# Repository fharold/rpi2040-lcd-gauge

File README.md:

# universal_gauges

Basic and versatile gauges based on the WAVESHARE RP2040-LCD-1.28 module.
A small HAT enhances it:

- 2 analog sensor inputs (divider stuffed to suit the sender, 5 V supply)
- 2 digital inputs (level shifted)
- 1 ambient light sensor
- 1 button
- 2 relay outputs

The firmware sources are in the repository root; the HAT itself is a KiCad
project in `pcb/`, described in [The HAT board](#the-hat-board).

The target is the **RP2040-LCD-1.28**. The touch variant is not supported: its
user button sits on GP16, which the HAT uses for its first digital input, so
the two would share one pin.

## Pinout

Signals added by the HAT:

| GPIO | Signal | Direction |
| ---- | ------ | --------- |
| GP16 | shifted_digital_in1 | input |
| GP17 | shifted_digital_in2 | input |
| GP18 | button_input | input, pull-up |
| GP19 | relay1_command_pin | output |
| GP20 | relay2_command_pin | output |
| GP26 | als_out | analog input, ADC0 |
| GP27 | sensor2_filtered | analog input, ADC1 |
| GP28 | sensor1_filtered | analog input, ADC2 |

The RP2040 ADC channel is not the GPIO number: GP26 is ADC0, GP27 is ADC1,
GP28 is ADC2, and GP29 (ADC3) is the module's own battery sense.

Pins used by the module itself (display, I2C, IMU, backlight, battery) are
defined in `lib/lcd/lcd.h`.

## The HAT board

The HAT is a KiCad 10 project, `pcb/rpi2040-lcd-gauge.kicad_pro`: a two-layer
board, 1.6 mm, 35 x 38.7 mm, whose lower edge is a semicircle following the
module. It sits
behind the RP2040-LCD-1.28 and connects to it through J2, a 2x10 1.27 mm
header. J1 is the header on the other side of the module; it is mechanical
only, none of its pads is connected.

The schematic is hierarchical, one sheet per function:

| Sheet | File | Contents |
| ----- | ---- | -------- |
| psu | `PSU.kicad_sch` | input protection, 12 V -> 5 V buck |
| ain_1, ain_2 | `sensor_1.kicad_sch`, `sensor_2.kicad_sch` | analog input dividers |
| din_1, din_2 | `digital_in_1.kicad_sch`, `digital_in_2.kicad_sch` | level-shifted digital inputs |
| relay_1, relay_2 | `output_relay_1.kicad_sch`, `relay.kicad_sch` | low-side relay drivers |
| als | `als.kicad_sch` | ambient light sensor |
| switch | `switch.kicad_sch` | push button |

### Connectors

All field wiring is on JST XH connectors, 2.5 mm pitch.

| Ref | Type | Pin 1 | Pin 2 | Pin 3 | Pin 4 |
| --- | ---- | ----- | ----- | ----- | ----- |
| J5 | XH 4 | GND | digital_in1 | digital_in2 | +12 V in |
| J7 | XH 3 | sensor1 signal | GND | +5 V out | |
| J8 | XH 3 | sensor2 signal | GND | +5 V out | |
| J3 | XH 2 | +12 V | relay1 coil, low-side switched | | |
| J4 | XH 2 | +12 V | relay2 coil, low-side switched | | |

J2 carries GP16-GP22 to the module, +5 V to it, 3.3 V back from it, and GND.

### Power

The 12 V input passes through F1 (1 A), Q1 (P-channel MOSFET, reverse polarity
protection) and D2 (SMBJ36A TVS) onto the protected +12 V rail, which also
feeds the relay connectors. U1, an LMR16006 buck with L1 (22 uH) and the
R2/R3 feedback divider (54k9 / 10k), makes 5 V from that rail and supplies the
module through J2. The 3.3 V used by the ambient light sensor comes back from
the module's own regulator.

### Input and output stages

**Analog inputs.** Each is a divider to GND: R15 in series, the ADC pin, then
R16 to ground (R17/R18 on the second channel). **The two resistors are stuffed
to suit the sender the board is built for**, so a board and the firmware
variant flashed on it have to match.

*Pressure board, R15 = R16 = 100 k.* The sender has a voltage output and the
divider simply halves it: a 0.5-4.5 V sender spans 250-2250 mV at the pin.
Source impedance there is 50 k.

*Temperature board, R15 = 6 k, R16 = 10 k.* The sender is resistive and wired
between the connector's +5 V and its signal pin, so it becomes the top of the
divider and the pin reads

    V = 5 V x 10k / (R_sender + 16k)

which is 3.125 V with the sender shorted — comfortably under the 3.3 V full
scale — and 0 V with it open or its wire broken. Source impedance runs 4 to
7 k over the sender's range.

**Digital inputs.** Each is clamped by an SMAJ18A, divided 10 k / 100 k,
clamped again by a BZX84C12, and drives the gate of a BSS138 whose drain is
the GPIO, pulled up to 3.3 V through 10 k with 10 nF to GND. **The stage
inverts**: the GPIO reads low when the input is driven high, and idles high
when the input is open or grounded.

**Relay outputs.** GP19 and GP20 drive IRLML0060 MOSFETs through 1 k, with
100 k gate pulldowns, switching the low side of a coil fed from +12 V. There
is no flyback diode on the HAT: use a relay that has one built in, or fit one
across the coil.

**Button and light sensor.** SW1 pulls GP18 to GND, against the RP2040's
internal pull-up. U3, an SFH 5711 logarithmic light sensor, sinks its output
current into R11 (47 k) on GP26.

### Fabrication

`pcb/gerber/` holds the plot exported from KiCad 10.0.5, also zipped as
`pcb/gerber.zip`: two copper layers, mask, silkscreen, paste, and the PTH and
NPTH drill files. `pcb/rpi2040-lcd-gauge.csv` is the BOM.

## Source layout

| File | Contents |
| ---- | -------- |
| `main.c` | bring-up order and the main loop, nothing else |
| `config.h` | every number you would tune: sensor spans, scales, backlight, sampling |
| `variant.h`, `variant.c` | the gauge variants, and the one this build selects |
| `board.h`, `board.c` | pin map, I2C scan, which of the two modules is running |
| `sensors.h`, `sensors.c` | ADC readings and their conversion to engineering units |
| `gauge.h`, `gauge.c` | frame buffer, gauge face and needle |
| `demo.h`, `demo.c` | the demo sweep, only compiled into a `USE_DEMO` build |
| `w.c`, `lib/` | widgets, drawing and display, from picoclock |

## Build variants

The firmware is built in three variants, selected at compile time by
`CURRENT_MODE`. One `cmake` + `make` builds all three:

| Variant | `CURRENT_MODE` | Gauge | Output |
| ------- | -------------- | ----- | ------ |
| engine oil temperature | `MODE_OIL_T` | 50-140 °C | `main_oil_t.uf2` |
| gearbox oil temperature | `MODE_GEARBOX_T` | 50-140 °C | `main_gearbox_t.uf2` |
| engine oil pressure | `MODE_OIL_P` | -0.5-6.5 bar | `main_oil_p.uf2` |

**The sensor is always wired to SENSOR1 (GP28), in every variant.** What the
variant changes is the input span applied to that reading, the quantity it
feeds, and the gauge face drawn behind the needle. It also has to match how
the board's input divider is stuffed, see
[Input and output stages](#input-and-output-stages). SENSOR2 is not used by any
variant; its pad is only configured as an analog input so it stays
high-impedance.

Each target is declared in `CMakeLists.txt` by the `universal_gauges_variant`
function. What separates one variant from another — input span, scale, reading
granularity and gauge face — is a `gauge_variant` structure. Adding a variant
means adding a `MODE_xxx` value in `variant.h`, one structure in `variant.c`
and one `universal_gauges_variant` call in `CMakeLists.txt`. Nothing else in
the firmware tests `CURRENT_MODE`.

### Calibration

All in `config.h`. Input spans, in millivolts, measured at the ADC pin:

| Define | Default | Meaning |
| ------ | ------- | ------- |
| `TEMP_SENSOR_MV_MIN` / `_MAX` | 1470 / 2960 | ends of the temperature curve below |
| `PRESSURE_SENSOR_MV_MIN` / `_MAX` | 250 / 2250 | pressure sensor output range |
| `ALS_MV_MIN` / `_MAX` | 0 / 2700 | ambient light sensor output range |

The temperature sender is an NTC and is nowhere near linear, so it is
described by `TEMP_SENSOR_CURVE`, a table of measured (mV, °C) points ordered
by rising mV:

| mV at GP28 | °C | sender |
| ---------- | -- | ------ |
| 1470 | 50 | 17.9 k |
| 1770 | 60 | 12.3 k |
| 2030 | 70 | 8.61 k |
| 2260 | 80 | 6.14 k |
| 2450 | 90 | 4.43 k |
| 2590 | 100 | 3.32 k |
| 2700 | 110 | 2.55 k |
| 2780 | 120 | 1.91 k |
| 2860 | 130 | 1.51 k |
| 2910 | 140 | 1.17 k |
| 2960 | 150 | 0.90 k |

Between two points the reading is interpolated, outside the table it is
clamped. `TEMP_SENSOR_MV_MIN` and `_MAX` have to stay equal to the first and
last mV of the table: they are what the percentage readout uses. Re-measuring
the sender means replacing the rows, nothing else. A variant whose
`gauge_variant` carries no curve — the pressure one — keeps the plain linear
span.

Display scales, in engineering units:

| Define | Default |
| ------ | ------- |
| `MIN_TEMP` / `MAX_TEMP` | 50 / 140 °C |
| `MIN_PRESS` / `MAX_PRESS` | -0.5 / 6.5 bar |

A reading below `_MIN` or above `_MAX` is clamped, not extrapolated. Change the
mV values to match a different sensor; change the unit values only if the gauge
face graduations change too. Note that the sender reaches 150 °C while the face
stops at 140: the needle parks on the last graduation above that.

The ADC is read every `ADC_PERIOD_MS` (100 ms), oversampled `ADC_SAMPLES` (8)
times per reading. The ambient light sensor drives the backlight between
`MIN_BRIGHTNESS` and `MAX_BRIGHTNESS`.

### Day and night

The same ambient light reading picks the gauge face: the `_dark` faces and the
orange needle below `THEME_NIGHT_BELOW` (20 %), the day faces and the red
needle above `THEME_DAY_ABOVE` (25 %).

| Define | Default | Meaning |
| ------ | ------- | ------- |
| `THEME_NIGHT_BELOW` | 20 | % of the ALS span under which the night face is used |
| `THEME_DAY_ABOVE` | 25 | % over which the day face is used |
| `THEME_HOLD_MS` | 2000 | how long a reading has to disagree with the face on screen |

Between the two thresholds nothing changes, so a reading sitting on the edge
cannot flip the face back and forth; set them equal for a plain single
threshold. On top of that the new reading has to hold for `THEME_HOLD_MS`
before the face is swapped, so a bridge or a row of trees does not repaint the
screen. A demo build holds the light at `DEMO_LIGHT_PERCENT` (100 %) and so
always shows the day face; lower it below 20 to look at the night one.

## Building the image

The Pico SDK is required, and CMake has to be able to find it:

`export PICO_SDK_PATH=/path/to/pico-sdk`

Alternatively, `export PICO_SDK_FETCH_FROM_GIT=1` lets CMake clone it. Then:

`mkdir build;cd build;cmake ..;make`

This produces the three `.uf2` files in `build/`.

## Demo mode

A demo build sweeps the needle across the face, end to end and back, and
ignores the sensor. It is the quick way to check a gauge face, the needle
geometry and the end stops with nothing wired to SENSOR1. It is off by
default and has to be asked for when configuring:

`mkdir build-demo;cd build-demo;cmake -DUSE_DEMO=ON ..;make`

Its targets are named `main_<variant>_demo`, so a demo image never overwrites
a real one and `pilo oil_t` can never pick one up by mistake. `pilo` takes them
under that name, and says so before flashing:

`./tool/pilo oil_t_demo`

The sweep takes `DEMO_SWEEP_MS` (4 s) each way with a `DEMO_HOLD_MS` (500 ms)
pause at each end, and the backlight is held at `DEMO_LIGHT_PERCENT` (100 %)
so the needle stays visible whatever the ambient light. The three are in
`config.h`. The analog inputs are still read and printed on the serial link,
so a demo build also shows whether the ADC side is alive, and the first line
it prints says `demo build`.

## Flashing the image

Put the board in BOOTSEL — hold BOOT while plugging it in, or double-tap reset,
as the build links `pico_bootsel_via_double_reset` — then:

`./tool/pilo oil_t`     engine oil temperature
`./tool/pilo gearbox_t` gearbox oil temperature
`./tool/pilo oil_p`     engine oil pressure

`./tool/pilo` with no argument lists the variants, their `_demo` counterparts
and where each `.uf2` was found. It warns when the sources are newer than the binary, and takes an
explicit file too: `./tool/pilo build/main_oil_p.uf2`. See
`tool/tools.md` for the environment overrides.

The equivalent by hand:

`picotool load ./build/main_oil_t.uf2 -x`

`sudo` is needed on Linux but not on macOS. With several boards connected,
list them with `picotool info -a` and target one with
`--bus <bus> --address <addr>`.

## Releases

Firmware images are not versioned in git; they are attached to GitHub
releases. Pushing a `v*` tag builds the three variants on GitHub and publishes
them:

`git tag v1.0.0 && git push origin v1.0.0`

The workflow is `.github/workflows/release.yml`. It also runs on
`workflow_dispatch`, and every run uploads the `.uf2` files as build
artifacts, so a build can be checked without publishing anything.

To publish from this machine instead — same three variants, built locally and
uploaded with the GitHub CLI:

`./tool/pirel v1.0.0`

`pirel` refuses to run on a dirty working tree, and passes extra arguments
through to `gh release create` (`--prerelease`, `--draft`, `--notes ...`).
Prefer the tag-triggered workflow for anything official: it does not depend on
this machine.

To flash an image downloaded from a release, give `pilo` its path:

`./tool/pilo ~/Downloads/main_oil_p.uf2`

## Tools

Scripts for flashing, releasing, serial shell, LCD screenshots, and converting
images and fonts into header files live in `tool/`, documented in
`tool/tools.md`. The images and fonts themselves are in `img/`, and the KiCad
project for the HAT is in `pcb/`.

## Known issues

- battery display has to be adjusted depending on battery type
- a broken sender wire reads a clean 0 mV, R16 pulling the pin down, and on a
  temperature board a shorted sender reads 3125 mV. Both fall outside the
  calibration, so both are recognisable, but the firmware only clamps them to
  the ends of the scale instead of showing a fault
- the analog inputs are named `SENSOR*_FILTERED` but there is no filter: no
  capacitor sits across the divider. On a pressure board it also presents 50 k
  to the ADC pin, more than the RP2040 would like; the 6 k / 10 k of a
  temperature board is fine
- nothing on a board says which sender it is stuffed for, and nothing stops
  `pilo` from flashing the wrong variant onto it
- the layout is one annotation behind the schematic. The catch diode is D7 in
  the schematic and still D4 on the board, which therefore carries two D4s,
  and SW1 is `SW` there. The gerbers were plotted before the last schematic
  edits, so re-annotate and re-plot before ordering
- the schematic and the BOM give R15 to R18 as 100 k, the pressure stuffing;
  the 6 k / 10 k of a temperature board is only written down in `config.h`

## Credits

Based on [dawigit/picoclock](https://github.com/dawigit/picoclock) — the
display, widget, drawing and font code, and the tooling in `tool/`, come from
that project.

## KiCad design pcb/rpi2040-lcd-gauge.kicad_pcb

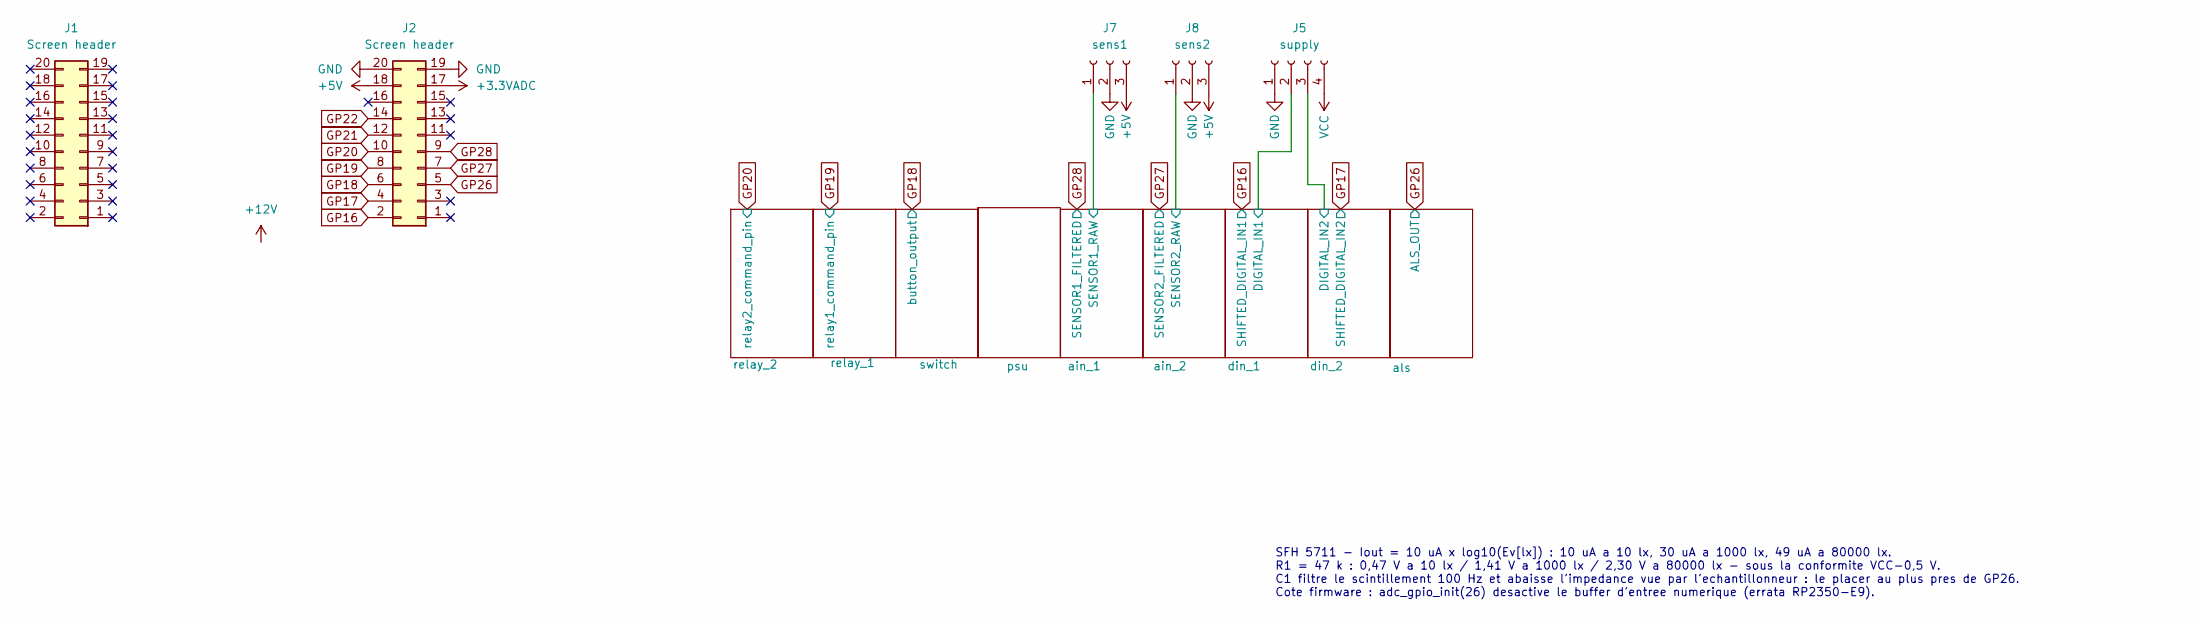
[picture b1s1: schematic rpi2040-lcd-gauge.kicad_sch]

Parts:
J1, J2: Screen header; PinHeader_2x10_P1.27mm_Vertical
J5: supply; JST_XH_B4B-XH-A_1x04_P2.50mm_Vertical
J7: sens1; JST_XH_B3B-XH-A_1x03_P2.50mm_Vertical
J8: sens2; JST_XH_B3B-XH-A_1x03_P2.50mm_Vertical

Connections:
+3.3VADC: J2.17; also elsewhere on the board
+5V: J2.18, J7.3, J8.3; also elsewhere on the board
/ain_1/SENSOR1_RAW: J7.1; also elsewhere on the board
/ain_2/SENSOR2_RAW: J8.1; also elsewhere on the board
/din_1/DIGITAL_IN1: J5.2; also elsewhere on the board
/din_2/DIGITAL_IN2: J5.3; also elsewhere on the board
GND: J2.19, J2.20, J5.1, J7.2, J8.2; also elsewhere on the board
GP16: J2.2; also elsewhere on the board
GP17: J2.4; also elsewhere on the board
GP18: J2.6; also elsewhere on the board
GP19: J2.8; also elsewhere on the board
GP20: J2.10; also elsewhere on the board
GP21: J2.12
GP22: J2.14
GP26: J2.5; also elsewhere on the board
GP27: J2.7; also elsewhere on the board
GP28: J2.9; also elsewhere on the board
VCC: J5.4; also elsewhere on the board

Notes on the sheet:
SFH 5711 - Iout = 10 uA x log10(Ev[lx]) : 10 uA a 10 lx, 30 uA a 1000 lx, 49 uA a 80000 lx. R1 = 47 k : 0,47 V a 10 lx / 1,41 V a 1000 lx / 2,30 V a 80000 lx - sous la conformite VCC-0,5 V. C1 filtre le scintillement 100 Hz et abaisse l'impedance vue par l'echantillonneur : le placer au plus pres d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

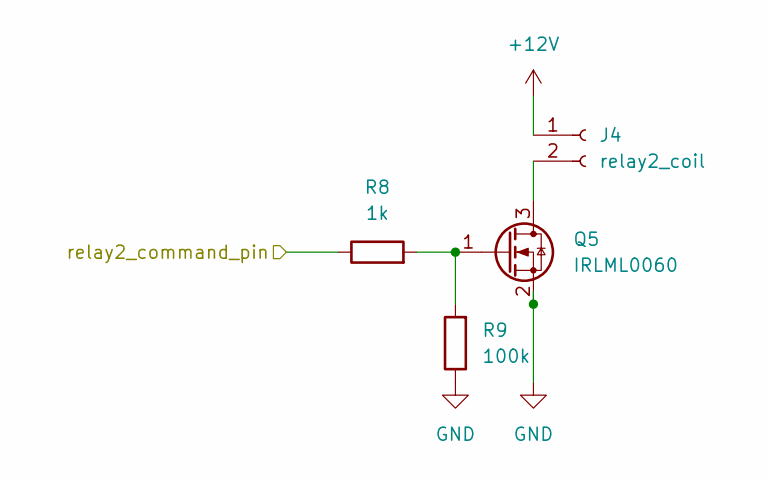
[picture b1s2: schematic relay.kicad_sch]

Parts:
J4: relay2_coil; JST_XH_B2B-XH-A_1x02_P2.50mm_Vertical
Q5: IRLML0060; SOT-23
R8: 1k; R_0805_2012Metric_Pad1.20x1.40mm_HandSolder
R9: 100k; R_0805_2012Metric_Pad1.20x1.40mm_HandSolder

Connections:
+12V: J4.1; also elsewhere on the board
GND: Q5.2 (S), R9.1; also elsewhere on the board
GP20: R8.1; also elsewhere on the board
unnamed: J4.2, Q5.3 (D)
unnamed: Q5.1 (G), R8.2, R9.2

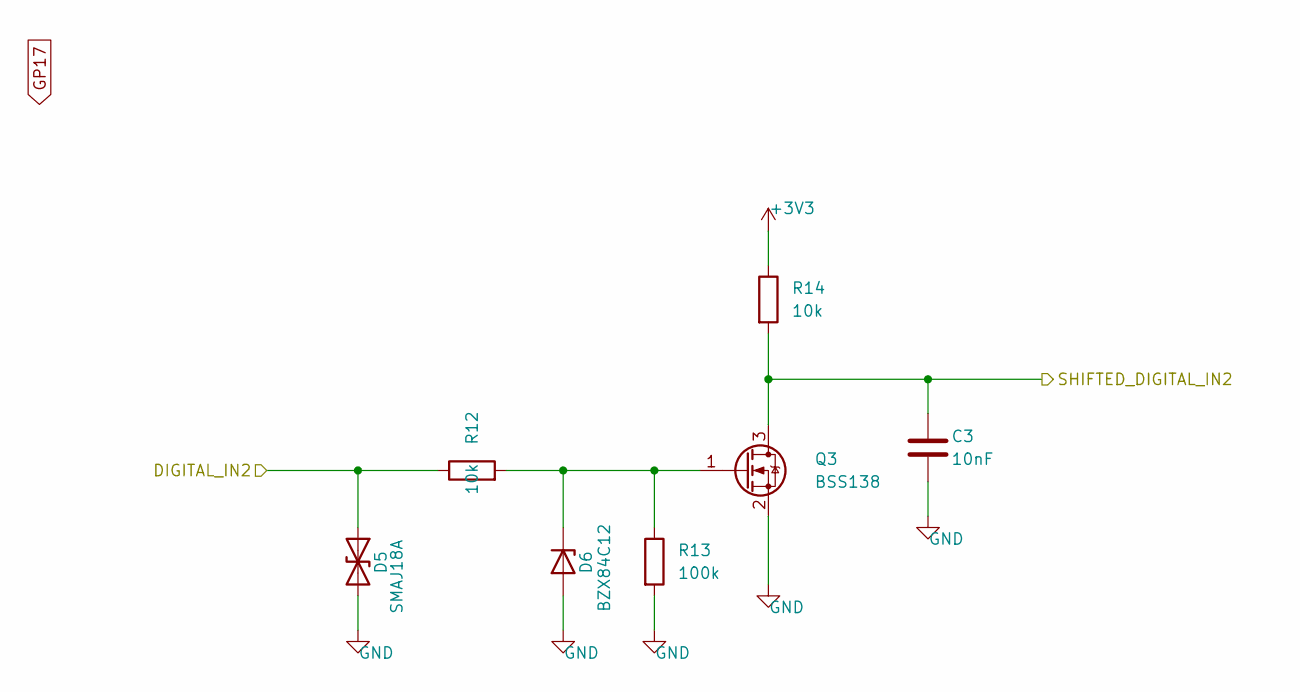
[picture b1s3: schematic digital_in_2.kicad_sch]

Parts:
C3: 10nF; R_0805_2012Metric_Pad1.20x1.40mm_HandSolder
D5: SMAJ18A; D_SMA
D6: BZX84C12; SOT-23
Q3: BSS138; SOT-23
R12, R14: 10k; R_0805_2012Metric_Pad1.20x1.40mm_HandSolder
R13: 100k; R_0805_2012Metric_Pad1.20x1.40mm_HandSolder

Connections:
+3V3: R14.1; also elsewhere on the board
/din_2/DIGITAL_IN2: D5.1 (A1), R12.1; also elsewhere on the board
GND: C3.2, D5.2 (A2), D6.2 (A), Q3.2 (S), R13.2; also elsewhere on the board
GP17: C3.1, Q3.3 (D), R14.2; also elsewhere on the board
unnamed: D6.1 (K), Q3.1 (G), R12.2, R13.1

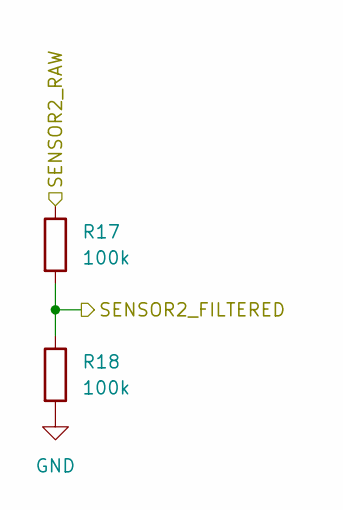
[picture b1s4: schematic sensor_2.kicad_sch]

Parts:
R17, R18: 100k; R_0805_2012Metric_Pad1.20x1.40mm_HandSolder

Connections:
/ain_2/SENSOR2_RAW: R17.1; also elsewhere on the board
GND: R18.2; also elsewhere on the board
GP27: R17.2, R18.1; also elsewhere on the board

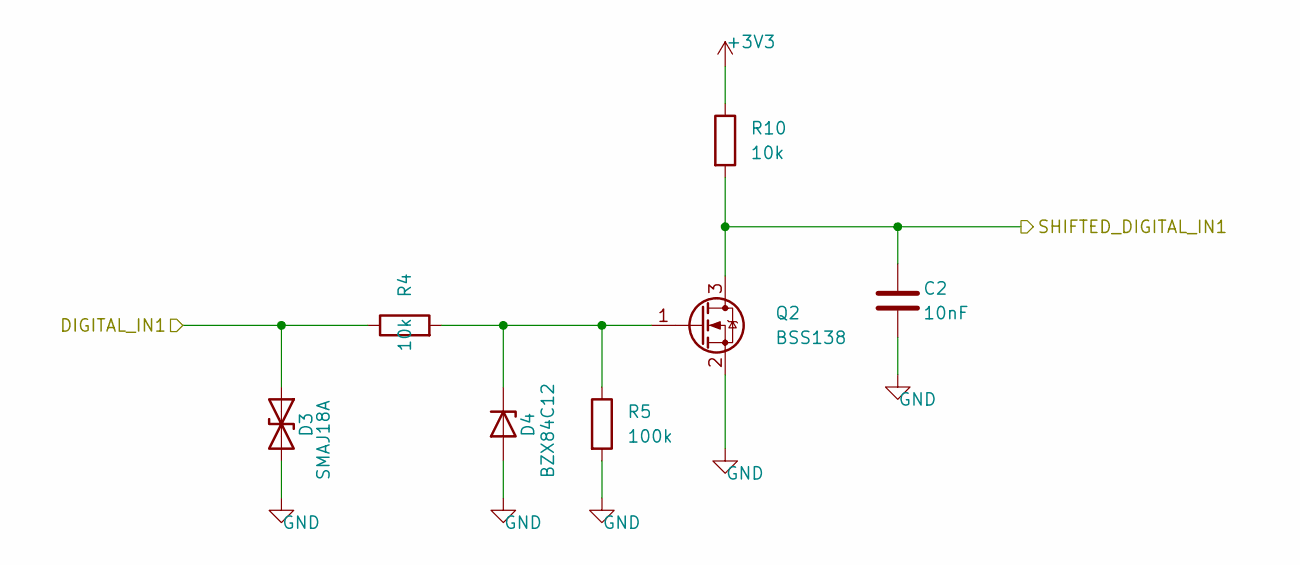
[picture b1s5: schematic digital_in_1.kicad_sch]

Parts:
C2: 10nF; R_0805_2012Metric_Pad1.20x1.40mm_HandSolder
D3: SMAJ18A; D_SMA
D4: BZX84C12; SOT-23
Q2: BSS138; SOT-23
R4, R10: 10k; R_0805_2012Metric_Pad1.20x1.40mm_HandSolder
R5: 100k; R_0805_2012Metric_Pad1.20x1.40mm_HandSolder

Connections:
+3V3: R10.1; also elsewhere on the board
/din_1/DIGITAL_IN1: D3.1 (A1), R4.1; also elsewhere on the board
GND: C2.2, D3.2 (A2), D4.2 (A), Q2.2 (S), R5.2; also elsewhere on the board
GP16: C2.1, Q2.3 (D), R10.2; also elsewhere on the board
unnamed: D4.1 (K), Q2.1 (G), R4.2, R5.1

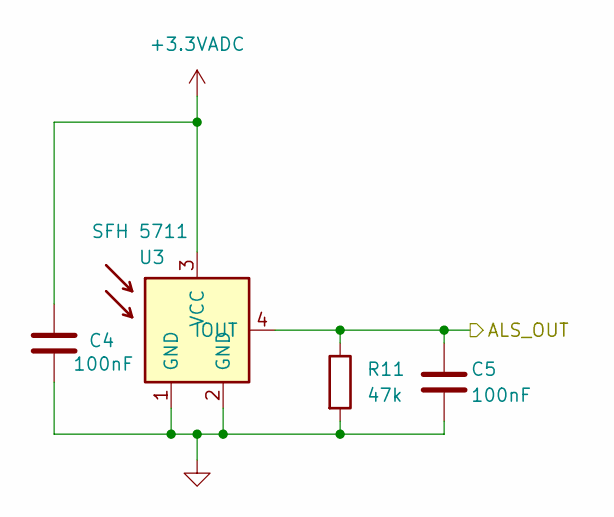
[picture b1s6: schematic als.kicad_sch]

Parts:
C4, C5: 100nF; R_0805_2012Metric_Pad1.20x1.40mm_HandSolder
R11: 47k; R_0805_2012Metric_Pad1.20x1.40mm_HandSolder
U3: SFH 5711

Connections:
+3.3VADC: C4.1, U3.3 (VCC); also elsewhere on the board
GND: C4.2, C5.2, R11.2, U3.1 (GND), U3.2 (GND); also elsewhere on the board
GP26: C5.1, R11.1, U3.4 (IOUT); also elsewhere on the board

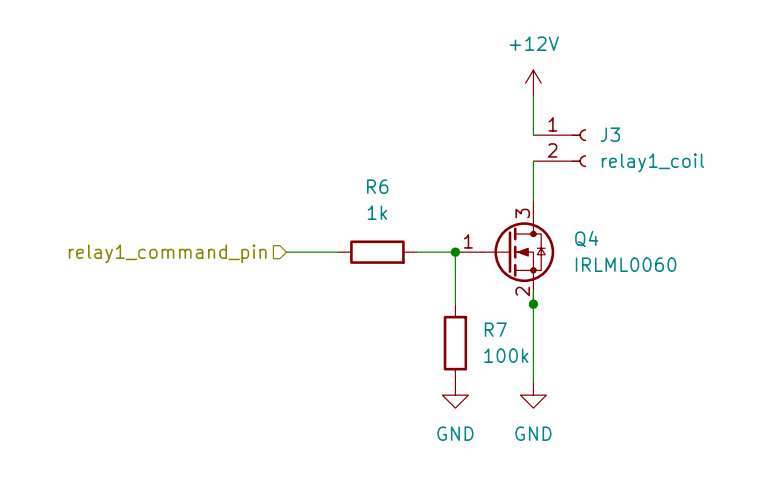
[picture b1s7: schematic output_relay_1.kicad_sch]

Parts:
J3: relay1_coil; JST_XH_B2B-XH-A_1x02_P2.50mm_Vertical
Q4: IRLML0060; SOT-23
R6: 1k; R_0805_2012Metric_Pad1.20x1.40mm_HandSolder
R7: 100k; R_0805_2012Metric_Pad1.20x1.40mm_HandSolder

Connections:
+12V: J3.1; also elsewhere on the board
GND: Q4.2 (S), R7.1; also elsewhere on the board
GP19: R6.1; also elsewhere on the board
unnamed: J3.2, Q4.3 (D)
unnamed: Q4.1 (G), R6.2, R7.2

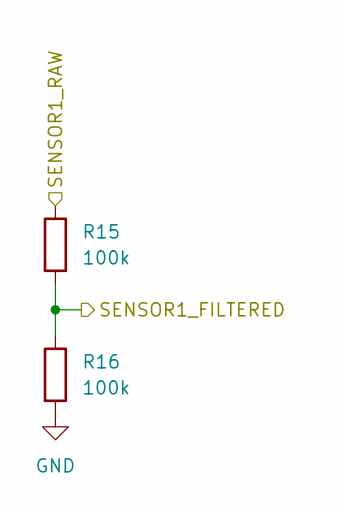
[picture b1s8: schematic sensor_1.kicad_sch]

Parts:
R15, R16: 100k; R_0805_2012Metric_Pad1.20x1.40mm_HandSolder

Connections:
/ain_1/SENSOR1_RAW: R15.1; also elsewhere on the board
GND: R16.2; also elsewhere on the board
GP28: R15.2, R16.1; also elsewhere on the board

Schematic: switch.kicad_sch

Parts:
SW1: SW_Push; SW_SPST_SKQG_WithoutStem

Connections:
GND: SW1.2; also elsewhere on the board
GP18: SW1.1; also elsewhere on the board

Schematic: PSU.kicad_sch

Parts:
C1: 4u7/100V; C_1206_3216Metric_Pad1.33x1.80mm_HandSolder
C6: 100n/100V; R_0805_2012Metric_Pad1.20x1.40mm_HandSolder
C7: 100n; R_0805_2012Metric_Pad1.20x1.40mm_HandSolder
C8: 22u/16V; C_1206_3216Metric_Pad1.33x1.80mm_HandSolder
C9: 100n/16V; C_1206_3216Metric_Pad1.33x1.80mm_HandSolder
D1: BZX84C15; SOT-23
D2: SMBJ36A; D_SMB
D7: B1100; D_SMA
F1: 1A; Fuse_1206_3216Metric
FB1: 600R/2A; L_1206_3216Metric_Pad1.22x1.90mm_HandSolder
L1: 22uH/1A; L_Bourns_SRN6045TA
Q1: P-MOS 100V; SOT-223-3_TabPin2
R1: 100k; R_0805_2012Metric_Pad1.20x1.40mm_HandSolder
R2: 54k9; R_0805_2012Metric_Pad1.20x1.40mm_HandSolder
R3: 10k; R_0805_2012Metric_Pad1.20x1.40mm_HandSolder
U1: LMR16006XDDCT; SOT-23-6

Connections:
+5V: C8.1, C9.1, L1.2, R2.2; also elsewhere on the board
+12V: D1.1 (K), D2.1 (A1), FB1.1, Q1.2 (S); also elsewhere on the board
GND: C1.2, C6.2, C8.2, C9.2, D2.2 (A2), D7.2 (A), R1.2, R3.2, U1.2 (GND); also elsewhere on the board
unnamed: D1.2 (A), Q1.1 (G), R1.1
unnamed: C7.2, D7.1 (K), L1.1, U1.6 (SW)
unnamed: F1.2, Q1.3 (D)
unnamed: C7.1, U1.1 (CB)
unnamed: R2.1, R3.1, U1.3 (FB)
unnamed: C1.1, C6.1, FB1.2, U1.5 (VIN)
VCC: F1.1; also elsewhere on the board

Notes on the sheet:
Alimentation 5 V / 300 mA - reseau de bord 12 V, apres-contact - LMR16006XDDCT en SOT-23-6 Q1 + R1 + D1 : inversion de polarite - D2 SMBJ36A : veille 36 V, bloquee pendant le load dump a 35 V / 400 ms U1 : 4 a 40 V continu, 65 V transitoire, 0,6 A, 700 kHz (595-805), asynchrone, SOT-23-6 sans plage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

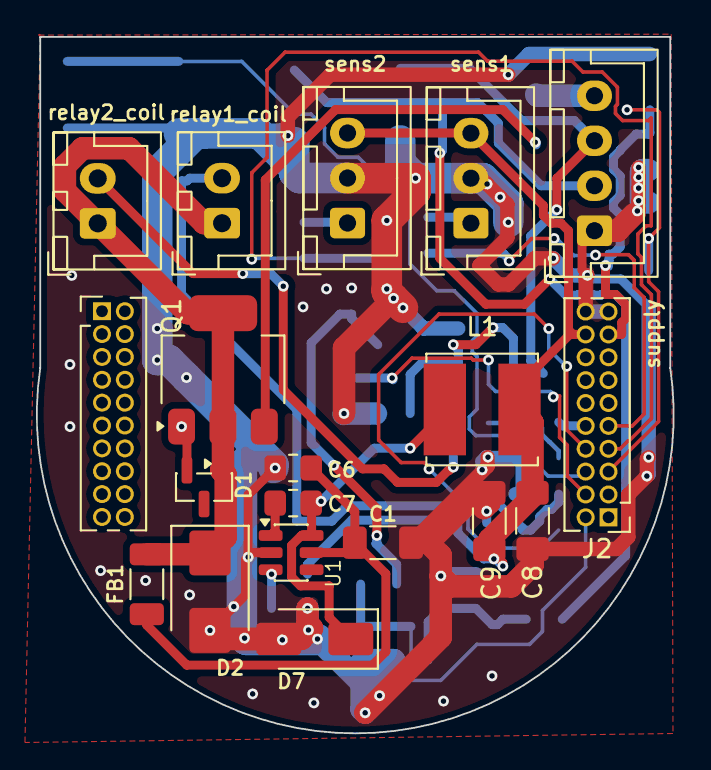
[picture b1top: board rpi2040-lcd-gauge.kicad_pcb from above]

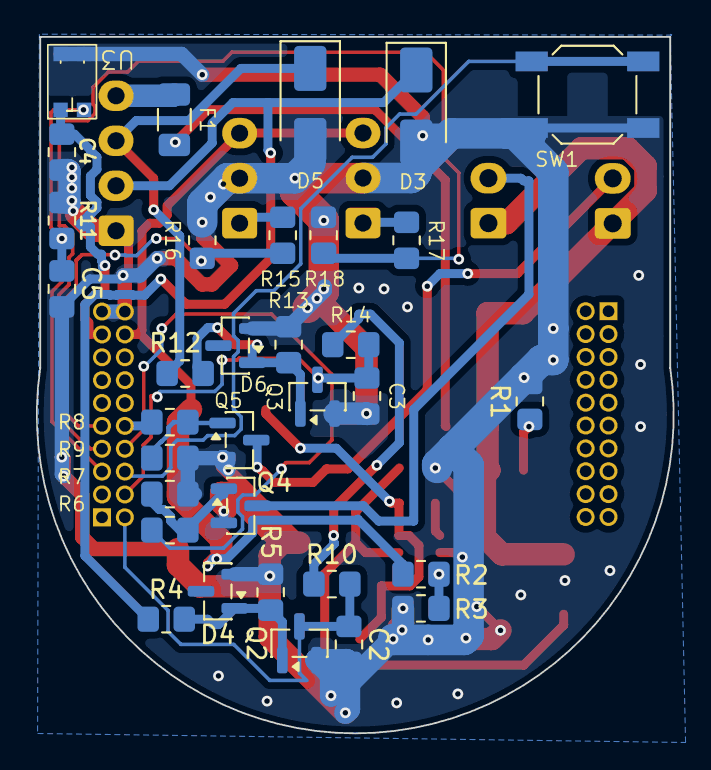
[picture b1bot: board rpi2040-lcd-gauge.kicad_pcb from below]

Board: 2 copper layers, 35.4 x 38.7 mm, 52 parts (33 on the bottom side), 30 nets.

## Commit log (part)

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2026-04-27 still trimming
2026-04-29 adding-resources
